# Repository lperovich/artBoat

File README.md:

# ArtBoat

Laura Perovich (perovich@media.mit.edu, www.lauraperovich.com) 
Object-based Media, MIT Media Lab

Code, hardware, and fabrication guides for ArtBoat, a community centered public art tool for light painting. A SeeBoat companion project.

LoRA radio (Adafruit Feather) communication with LED strip output.

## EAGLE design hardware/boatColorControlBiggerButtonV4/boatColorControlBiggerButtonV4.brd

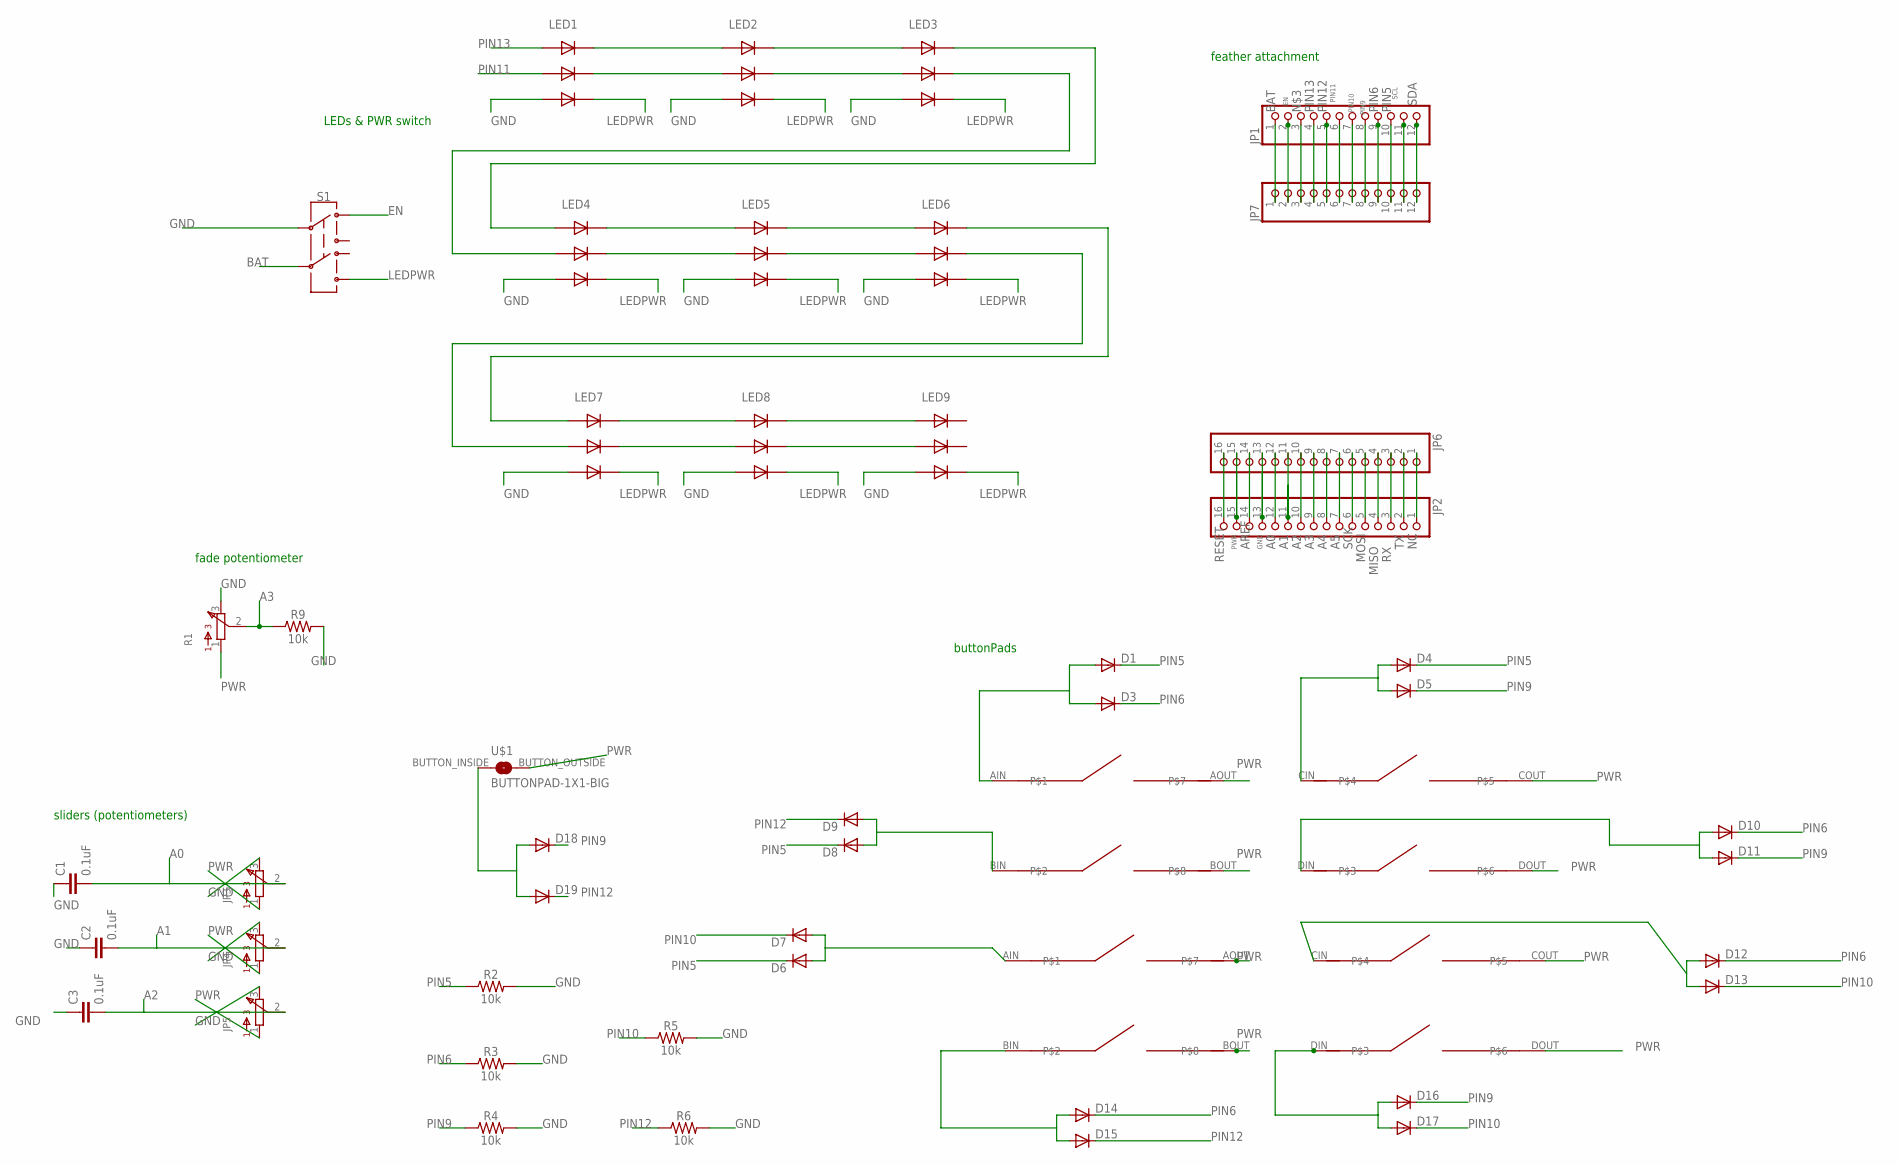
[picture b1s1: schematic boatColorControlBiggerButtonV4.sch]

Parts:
C1, C2, C3: 0.1uF; 0603
D1, D3, D4, D5, D6, D7, D8, D9, D10, D11, D12, D13, D14, D15, D16, D17, D18, D19: DIODESOD123; SOD123
JP1, JP7: PINHD-1X12; 1X12
JP2, JP6: PINHD-1X16; 1X16
JP3, JP4, JP5: BOURNESPOTENTIOMETER
LED1, LED2, LED3, LED4, LED5, LED6, LED7, LED8, LED9: RGBLED_DOTSTAR5050; RGBLED5050_DOTSTAR
R1: PTV_BOURNES_POT; PVT_BOURNES_POT
R2, R3, R4, R5, R6, R9: 10k; 0603
S1: SWITCH-DPDT-PTH-GPI-152-3013; SWITCH_DPDT_CRFS-2202W
U$1: BUTTONPAD-1X1-BIG; BUTTONPAD-1X1
U$9, U$13: BUTTONPAD2X2; BUTTONPAD-2X2

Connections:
A0: C1.2, JP2.12, JP3.2, JP6.12
A1: C2.2, JP2.11, JP4.2, JP6.11
A2: C3.2, JP2.10, JP5.2, JP6.10
A3: JP2.9, JP6.9, R1.2, R9.1
A4: JP2.8, JP6.8
A5: JP2.7, JP6.7
AREF: JP2.14, JP6.14
BAT: JP1.1, JP7.1, S1.C@2 (5)
EN: JP1.2, JP7.2, S1.10 (1)
GND: C1.1, C2.1, C3.1, JP2.13, JP3.3, JP4.3, JP5.3, JP6.13, LED1.GND, LED2.GND, LED3.GND, LED4.GND, LED5.GND, LED6.GND, LED7.GND, LED8.GND, LED9.GND, R1.3, R2.2, R3.2, R4.2, R5.2, R6.2, R9.2, S1.C@1 (2)
LEDPWR: LED1.VCC, LED2.VCC, LED3.VCC, LED4.VCC, LED5.VCC, LED6.VCC, LED7.VCC, LED8.VCC, LED9.VCC, S1.21 (6)
MISO: JP2.4, JP6.4
MOSI: JP2.5, JP6.5
unnamed: JP1.3, JP7.3
unnamed: LED1.DATAOUT, LED2.DATAIN
unnamed: LED1.CLOCKOUT, LED2.CLOCKIN
unnamed: LED2.DATAOUT, LED3.DATAIN
unnamed: LED2.CLOCKOUT, LED3.CLOCKIN
unnamed: LED4.DATAOUT, LED5.DATAIN
unnamed: LED4.CLOCKOUT, LED5.CLOCKIN
unnamed: LED5.DATAOUT, LED6.DATAIN
unnamed: LED5.CLOCKOUT, LED6.CLOCKIN
unnamed: LED7.DATAOUT, LED8.DATAIN
unnamed: LED7.CLOCKOUT, LED8.CLOCKIN
unnamed: LED8.DATAOUT, LED9.DATAIN
unnamed: LED8.CLOCKOUT, LED9.CLOCKIN
unnamed: LED3.CLOCKOUT, LED4.CLOCKIN
unnamed: LED3.DATAOUT, LED4.DATAIN
unnamed: LED6.DATAOUT, LED7.DATAIN
unnamed: LED6.CLOCKOUT, LED7.CLOCKIN
unnamed: D1.ANODE (A), D3.ANODE (A), U$9.AIN
unnamed: D4.ANODE (A), D5.ANODE (A), U$9.CIN
unnamed: D6.ANODE (A), D7.ANODE (A), U$13.AIN
unnamed: D8.ANODE (A), D9.ANODE (A), U$9.BIN
unnamed: D10.ANODE (A), D11.ANODE (A), U$9.DIN
unnamed: D12.ANODE (A), D13.ANODE (A), U$13.CIN
unnamed: D14.ANODE (A), D15.ANODE (A), U$13.BIN
unnamed: D16.ANODE (A), D17.ANODE (A), U$13.DIN
unnamed: D18.ANODE (A), D19.ANODE (A), U$1.BUTTON_INSIDE (BUTTONINSIDE)
NC: JP2.1, JP6.1
PIN5: D1.CATHODE (C), D4.CATHODE (C), D6.CATHODE (C), D8.CATHODE (C), JP1.10, JP7.10, R2.1
PIN6: D3.CATHODE (C), D10.CATHODE (C), D12.CATHODE (C), D14.CATHODE (C), JP1.9, JP7.9, R3.1
PIN9: D5.CATHODE (C), D11.CATHODE (C), D16.CATHODE (C), D18.CATHODE (C), JP1.8, JP7.8, R4.1
PIN10: D7.CATHODE (C), D13.CATHODE (C), D17.CATHODE (C), JP1.7, JP7.7, R5.1
PIN11: JP1.6, JP7.6, LED1.CLOCKIN
PIN12: D9.CATHODE (C), D15.CATHODE (C), D19.CATHODE (C), JP1.5, JP7.5, R6.1
PIN13: JP1.4, JP7.4, LED1.DATAIN
PWR: JP2.15, JP3.1, JP4.1, JP5.1, JP6.15, R1.1, U$1.BUTTON_OUTSIDE (BUTTONOUTSIDE), U$9.AOUT, U$9.BOUT, U$9.COUT, U$9.DOUT, U$13.AOUT, U$13.BOUT, U$13.COUT, U$13.DOUT
RESET: JP2.16, JP6.16
RX: JP2.3, JP6.3
SCK: JP2.6, JP6.6
SCL: JP1.11, JP7.11
SDA: JP1.12, JP7.12
TX: JP2.2, JP6.2

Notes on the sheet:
LEDs & PWR switch
buttonPads
sliders (potentiometers)
feather attachment
fade potentiometer

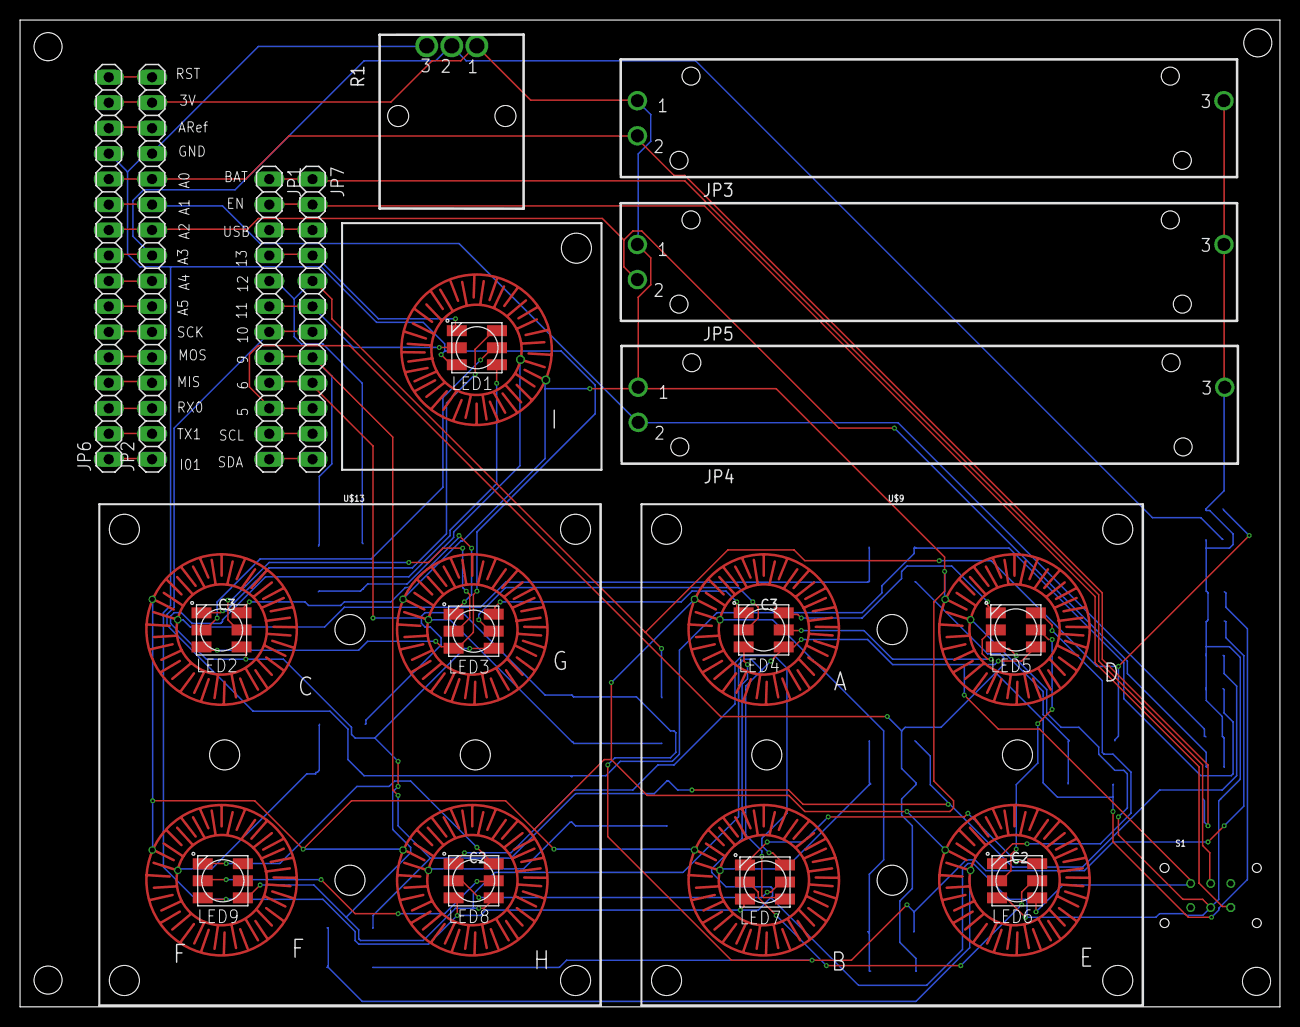
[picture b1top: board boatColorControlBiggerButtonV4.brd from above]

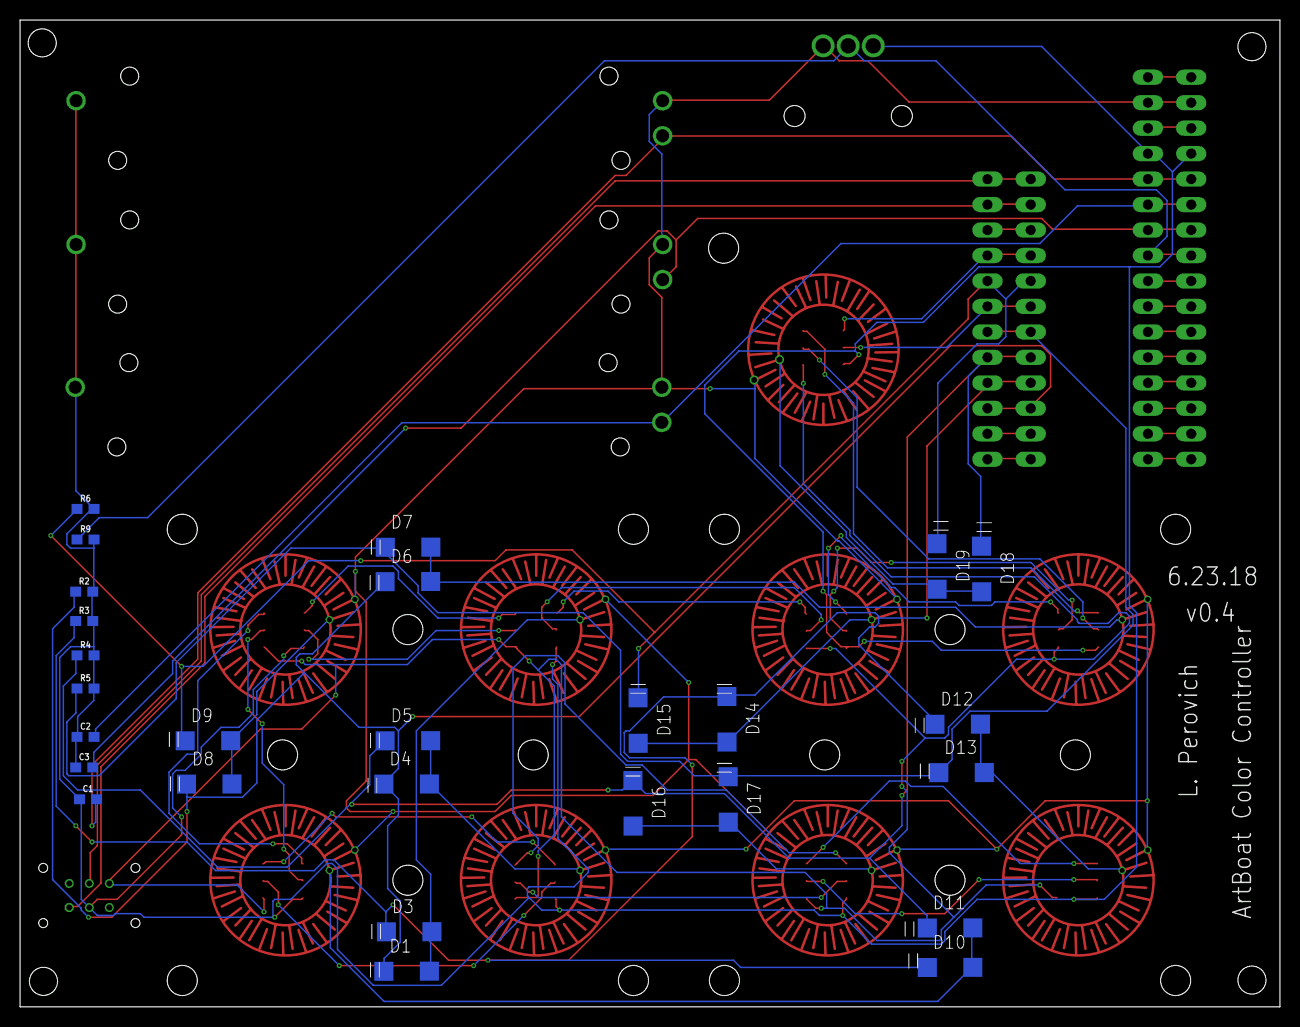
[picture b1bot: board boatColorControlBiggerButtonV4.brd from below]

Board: 2 copper layers, 125.7 x 98.4 mm, 48 parts (27 on the bottom side), 54 nets.

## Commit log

2018-06-26 software update
2018-06-27 hardware update
2018-07-12 add boat ID for multiple boats at once
2018-07-24 update parts lists w/header

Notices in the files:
parts and their libraries:
SparkFun-Capacitors: Licensing: Creative Commons ShareAlike 4.0 International - https://creativecommons.org/licenses/by-sa/4.0
